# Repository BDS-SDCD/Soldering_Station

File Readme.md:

# MAIN

 This soldering station developed for the handle of the Hakko T12 soldering iron (needs to be modified according to the given scheme) Heat gun with the 8858 substation (~220 spiral 12V fan). Anything that can heat up from ~220 and has a thermocouple will do as a soldering separator. In my case, it is literally an iron. This project was developed for home made one layer PCB based on photoresist technology and using the element base that is already available.<br/>

[Schematic](https://github.com/BDS-SDCD/Soldering_Station/tree/main/Station%20Schematic/Chematic%20PDF)<br/>
[Code](https://github.com/BDS-SDCD/Soldering_Station/tree/main/Station%20Code/Core)<br/>

### Features

 Each of the devices has a set of settings. As a rule, when I’m working with a soldering station, I use only a few temperature settings, which are implemented here in adjustable temperature presets. Each of the presets has its own temperature correction value, which allows you to accurately adjust the temperature of each preset. Also, the manual control mode has a separate temperature correction value.

In this project I did not provide the ability to configure important parameters such as the PID controller coefficient and the temperature conversion coefficient in the user interface. All this can be configured in the [Soldering_Station.h](https://github.com/BDS-SDCD/Soldering_Station/blob/main/Station%20Code/Core/Inc/Soldering_Station.h) file by changing the Define value. Also you can change Button mapping of presets in this file. Everything else is configured inside the user interface.

All interfaces are symbolic.

 Switching on/off any soldering device can be done either by additional methods or by short pressing the encoder. Switching control between the heat gun and the soldering separator can be done by holding the encoder SW1. Switching temperature settings as well as setting the temperature of the manual mode is done only when the soldering device is turned on.

 Holding the SW4 encoder will lead to the transition to the menu with devices and their parameters. The transition from the menu to the previous menu is carried out by holding the SW4 encoder. When setting the value, several step modifiers are available by pressing buttons SW8 and SW2. The standard value is x1. When pressing button SW8, the modifier changes to x2. When you press SW8 button again, the modifier will return. SW8 button with the x5 modifier works the same way. If you turn on 2 modifiers in a free order, you will get a x10 modifier.

### Soldering iron

 The advantages include the fact that, unlike the original Chinese Hakko T12 controller, you will no longer be able to hear annoying clicks during heating, since here PWM is used to control the soldering iron. The PWM frequency is 24 kHz. Unlike the basic version of the soldering iron controller, it has the ability to press a button on the soldering iron to set the maximum temperature for heating massive soldering pads. The implementation of the button is the setting of the maximum temperature that the ADC can process. When implementing the supply of full power without regulation, it led me to several broken soldering tips.

### Soldering Heat Gun

 As a control system for heating the heat gun, as well as the soldering separator, the Phase Angle Control(PAC) system is used. The control module for the air flow rate of the heat gun is completely linear and analog, which leads to the need to install a radiator on the MOSFET. Setting the minimum flow rate(RV6), as well as the maximum flow rate(RV4), is adjusted by variable resistors. A separate variable resistor is used to control the manual flow rate(RV3). The system automatically sets the maximum air flow rate during the cooling of the heat gun after switching off. Switching on/off can be done either from the control panel or by uninstalling/installing the heat gun on the stand. Ideally, the power part of the heat gun control should be connected so that the phase is broken, which in this case will ensure safe contact with the socket with the soldering station connected to the power.

### Soldering separator.

 An old iron is used as a soldering separator in this project. This is the only test subject that survived many heating and cooling cycles, since the melting temperature of the soldering mouth is 187 degrees, and when soldering BGA chips, 270. Like the heat gun, the control system based on PAC. Switching on/off can be done either from the control panel.

### Update<br/>

The PAC implementation has been changed from software to hardware. The input capture and PAC system is implemented based on the signal capture and PWM modes. 

### Further development.

 The schematic provides for a ventilation control system. Since the Hakko T12 soldering iron can be modified similarly to the 908b Soldering iron smoke absorber. Since the project is being done primarily for myself, I have not yet decided which type of ventilation will be more convenient for me.

 In the future, schematic of this module will be changed depending on my experience of use. At those moment, there is no software implementation of this unit.
In case of inconvenience during regular work, modification or replacement of the symbolic interface with a graphical one.
Also, if necessary, other functionality will be added.

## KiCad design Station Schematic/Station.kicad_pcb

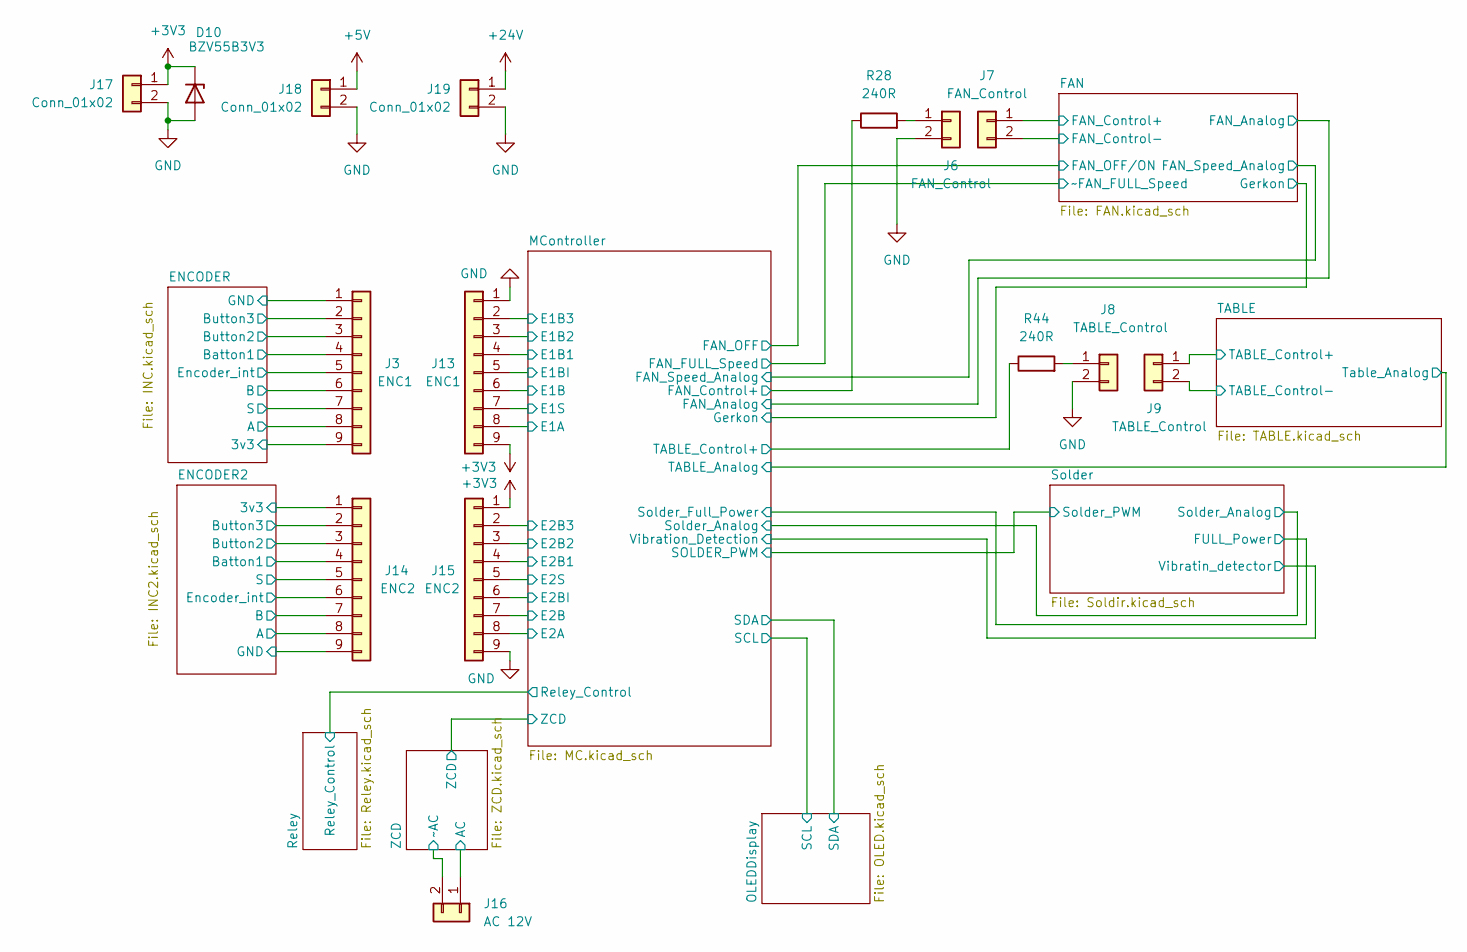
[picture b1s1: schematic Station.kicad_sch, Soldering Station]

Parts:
D10: BZV55B3V3; D_MiniMELF
J3: ENC1; PinSocket_1x09_P2.54mm_Vertical
J6: FAN_Control; PinHeader_1x02_P2.54mm_Vertical
J7: FAN_Control; PinSocket_1x02_P2.54mm_Vertical
J8: TABLE_Control; PinHeader_1x02_P2.54mm_Vertical
J9: TABLE_Control; PinSocket_1x02_P2.54mm_Vertical
J13: ENC1; PinHeader_1x09_P2.54mm_Vertical
J14: ENC2; PinSocket_1x09_P2.54mm_Vertical
J15: ENC2; PinHeader_1x09_P2.54mm_Vertical
J16: AC 12V; TerminalBlock_4Ucon_1x02_P3.50mm_Horizontal
J17, J18, J19: Conn_01x02; PhoenixContact_GMSTBVA_2,5_2-G_1x02_P7.50mm_Vertical
R28, R44: 240R; R_1206_3216Metric_Pad1.30x1.75mm_HandSolder

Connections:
+3V3: D10.1 (K), J13.9, J15.1, J17.1; also elsewhere on the board
+5V: J18.1; also elsewhere on the board
+24V: J19.1; also elsewhere on the board
/ENCODER2/3v3: J14.1; also elsewhere on the board
/ENCODER2/A: J14.8; also elsewhere on the board
/ENCODER2/B: J14.7; also elsewhere on the board
/ENCODER2/Batton1: J14.4; also elsewhere on the board
/ENCODER2/Button2: J14.3; also elsewhere on the board
/ENCODER2/Button3: J14.2; also elsewhere on the board
/ENCODER2/Encoder_int: J14.6; also elsewhere on the board
/ENCODER2/GND: J14.9; also elsewhere on the board
/ENCODER2/S: J14.5; also elsewhere on the board
/ENCODER/3v3: J3.9; also elsewhere on the board
/ENCODER/A: J3.8; also elsewhere on the board
/ENCODER/B: J3.6; also elsewhere on the board
/ENCODER/Batton1: J3.4; also elsewhere on the board
/ENCODER/Button2: J3.3; also elsewhere on the board
/ENCODER/Button3: J3.2; also elsewhere on the board
/ENCODER/Encoder_int: J3.5; also elsewhere on the board
/ENCODER/GND: J3.1; also elsewhere on the board
/ENCODER/S: J3.7; also elsewhere on the board
/FAN/FAN_Control+: J7.1; also elsewhere on the board
/FAN/FAN_Control-: J7.2; also elsewhere on the board
/MController/E1A: J13.8; also elsewhere on the board
/MController/E1B: J13.6; also elsewhere on the board
/MController/E1B1: J13.4; also elsewhere on the board
/MController/E1B2: J13.3; also elsewhere on the board
/MController/E1B3: J13.2; also elsewhere on the board
/MController/E1BI: J13.5; also elsewhere on the board
/MController/E1S: J13.7; also elsewhere on the board
/MController/E2A: J15.8; also elsewhere on the board
/MController/E2B: J15.7; also elsewhere on the board
/MController/E2B1: J15.4; also elsewhere on the board
/MController/E2B2: J15.3; also elsewhere on the board
/MController/E2B3: J15.2; also elsewhere on the board
/MController/E2BI: J15.6; also elsewhere on the board
/MController/E2S: J15.5; also elsewhere on the board
/MController/FAN_Control+: R28.1; also elsewhere on the board
/MController/TABLE_Control+: R44.1; also elsewhere on the board
/TABLE/TABLE_Control+: J9.1; also elsewhere on the board
/TABLE/TABLE_Control-: J9.2; also elsewhere on the board
/ZCD/AC: J16.1; also elsewhere on the board
/ZCD/~AC: J16.2; also elsewhere on the board
GND: D10.2 (A), J6.2, J8.2, J13.1, J15.9, J17.2, J18.2, J19.2; also elsewhere on the board
unnamed: J6.1, R28.2
unnamed: J8.1, R44.2

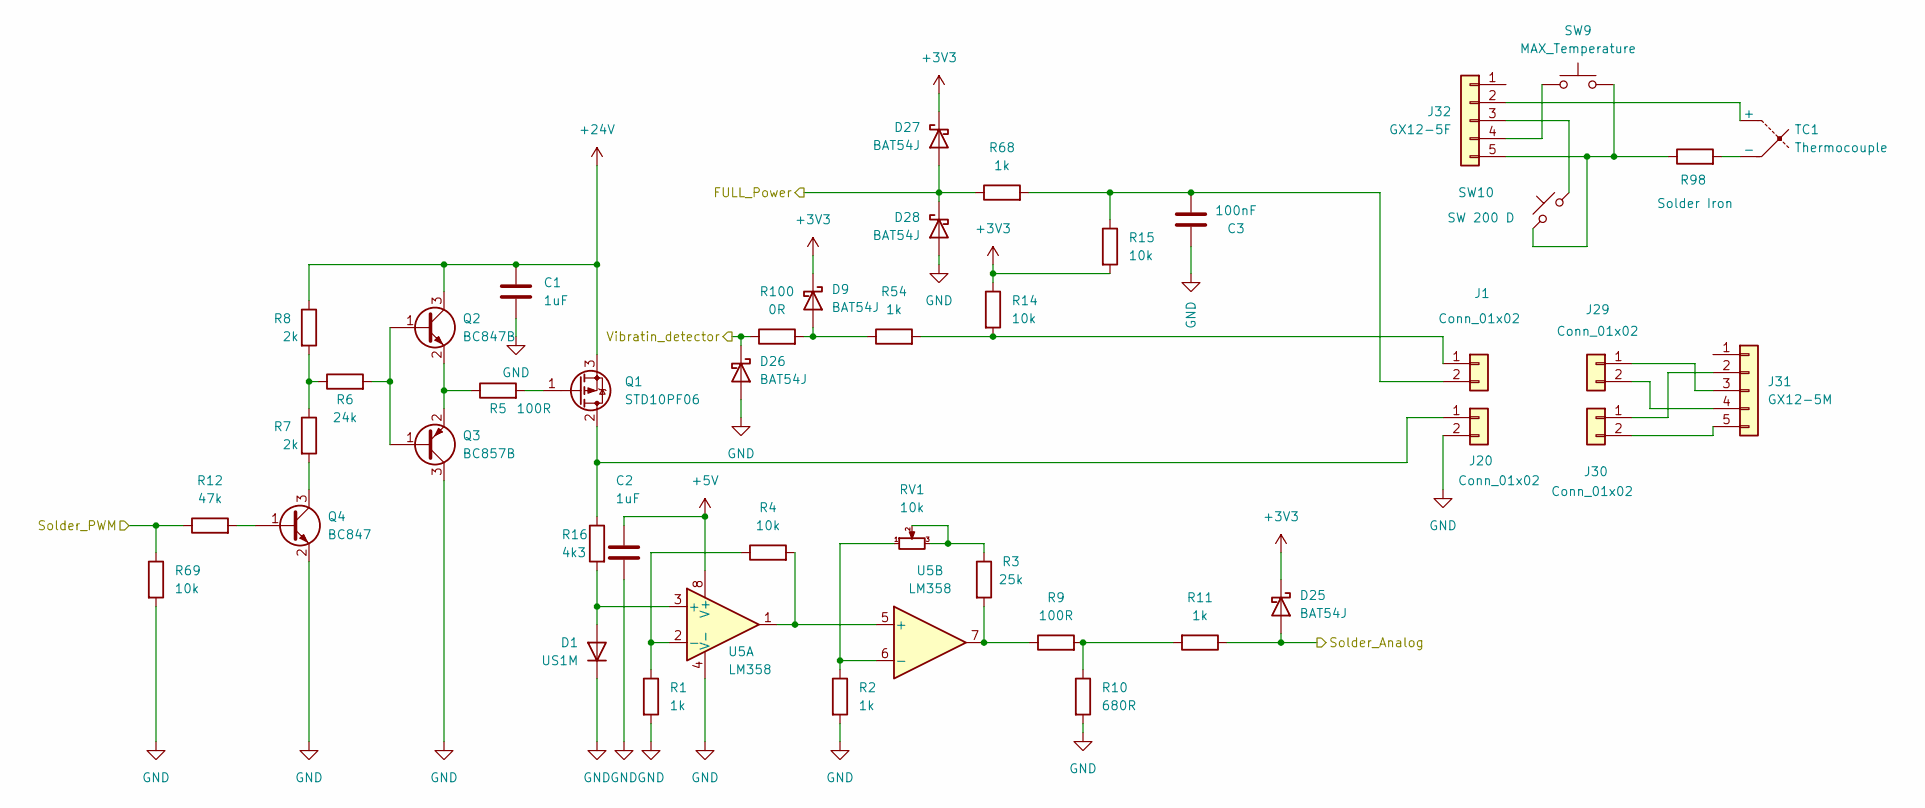
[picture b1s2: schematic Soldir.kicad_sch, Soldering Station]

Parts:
C1, C2: 1uF; C_1206_3216Metric
C3: 100nF; C_1206_3216Metric
D1: US1M; D_SMA
D9, D25, D26, D27, D28: BAT54J; D_SOD-323F
J1, J29: Conn_01x02; PinHeader_1x02_P2.54mm_Vertical
J20, J30: Conn_01x02; PhoenixContact_GMSTBVA_2,5_2-G_1x02_P7.50mm_Vertical
J31: GX12-5M
J32: GX12-5F
Q1: STD10PF06; TO-252-2
Q2: BC847B; TSOT-23
Q3: BC857B; TSOT-23
Q4: BC847; TSOT-23
R1, R2, R11, R54, R68: 1k; R_1206_3216Metric_Pad1.30x1.75mm_HandSolder
R3: 25k; R_1206_3216Metric_Pad1.30x1.75mm_HandSolder
R4, R14, R15, R69: 10k; R_1206_3216Metric_Pad1.30x1.75mm_HandSolder
R5, R9: 100R; R_1206_3216Metric_Pad1.30x1.75mm_HandSolder
R6: 24k; R_1206_3216Metric_Pad1.30x1.75mm_HandSolder
R7, R8: 2k; R_1206_3216Metric_Pad1.30x1.75mm_HandSolder
R10: 680R; R_1206_3216Metric_Pad1.30x1.75mm_HandSolder
R12: 47k; R_1206_3216Metric_Pad1.30x1.75mm_HandSolder
R16: 4k3; R_1206_3216Metric_Pad1.30x1.75mm_HandSolder
R98: Solder Iron
R100: 0R; R0 16.128
RV1: 10k; Potentiometer_Bourns_3266Y_Vertical
SW9: MAX_Temperature
SW10: SW 200 D
TC1: Thermocouple
U5: LM358; SOIC-8_3.9x4.9mm_P1.27mm

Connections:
+3V3: D9.1 (K), D25.1 (K), D27.1 (K), R14.1, R15.2; also elsewhere on the board
+5V: C2.1, U5.8 (V+); also elsewhere on the board
+24V: C1.1, Q1.3 (S1), Q2.3 (C), R8.1; also elsewhere on the board
/MController/SOLDER_PWM: R12.1, R69.1; also elsewhere on the board
/MController/Solder_Analog: D25.2 (A), R11.1; also elsewhere on the board
/MController/Solder_Full_Power: D27.2 (A), D28.1 (K), R68.1; also elsewhere on the board
/MController/Vibration_Detection: D26.1 (K), R100.1; also elsewhere on the board
GND: C1.2, C2.2, C3.2, D1.1 (K), D26.2 (A), D28.2 (A), J20.2, Q3.3 (C), Q4.2 (E), R1.2, R2.2, R10.2, R69.2, U5.4 (V-); also elsewhere on the board
unnamed: D1.2 (A), R16.2, U5.3 (+)
unnamed: D9.2 (A), R54.1, R100.2
unnamed: J1.1, R14.2, R54.2
unnamed: C3.1, J1.2, R15.1, R68.2
unnamed: J20.1, Q1.2 (D1), R16.1
unnamed: J29.1, J31.3
unnamed: J29.2, J31.4
unnamed: J30.1, J31.2
unnamed: J30.2, J31.5
unnamed: J32.2, TC1.1 (+)
unnamed: J32.3, SW10.2
unnamed: J32.4, SW9.1
unnamed: J32.5, R98.1, SW9.2, SW10.1
unnamed: Q1.1 (G2), R5.2
unnamed: Q2.1 (B), Q3.1 (B), R6.2
unnamed: Q2.2 (E), Q3.2 (E), R5.1
unnamed: Q4.1 (B), R12.2
unnamed: Q4.3 (C), R7.2
unnamed: R3.1, RV1.2, RV1.3
unnamed: R3.2, R9.1, U5.7
unnamed: R6.1, R7.1, R8.2
unnamed: R9.2, R10.1, R11.2
unnamed: R98.2, TC1.2 (-)
unnamed: R1.1, R4.1, U5.2 (-)
unnamed: R4.2, U5.1, U5.5 (+)
unnamed: R2.1, RV1.1, U5.6 (-)

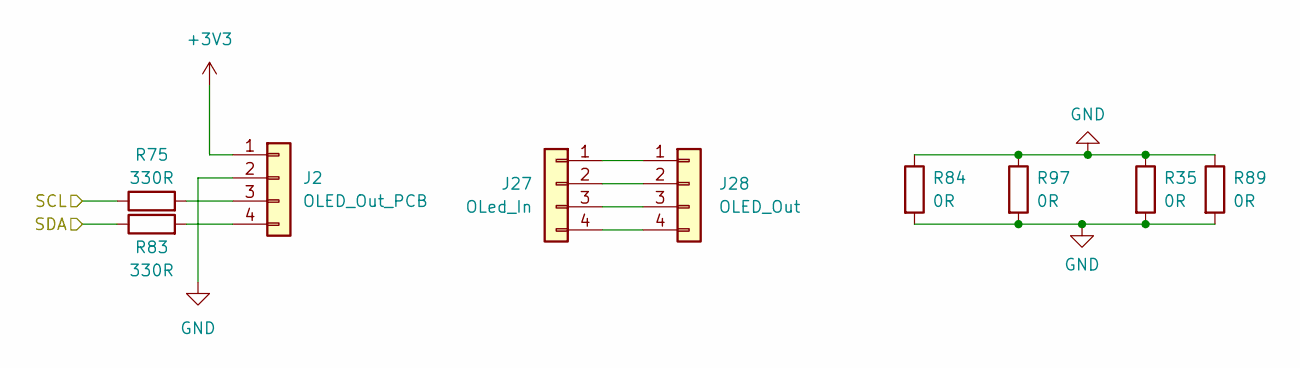
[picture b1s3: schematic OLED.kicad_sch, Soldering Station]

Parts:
J2: OLED_Out_PCB; PinHeader_1x04_P2.54mm_Vertical
J27: OLed_In; PinHeader_1x04_P2.54mm_Vertical
J28: OLED_Out; PinSocket_1x04_P2.54mm_Vertical
R35, R84, R89, R97: 0R; R_1206_3216Metric_Pad1.30x1.75mm_HandSolder
R75, R83: 330R; R_1206_3216Metric_Pad1.30x1.75mm_HandSolder

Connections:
+3V3: J2.1; also elsewhere on the board
/MController/SCL: R75.1; also elsewhere on the board
/MController/SDA: R83.1; also elsewhere on the board
GND: J2.2, R35.1, R35.2, R84.1, R84.2, R89.1, R89.2, R97.1, R97.2; also elsewhere on the board
unnamed: J2.3, R75.2
unnamed: J2.4, R83.2
unnamed: J27.1, J28.1
unnamed: J27.2, J28.2
unnamed: J27.3, J28.3
unnamed: J27.4, J28.4

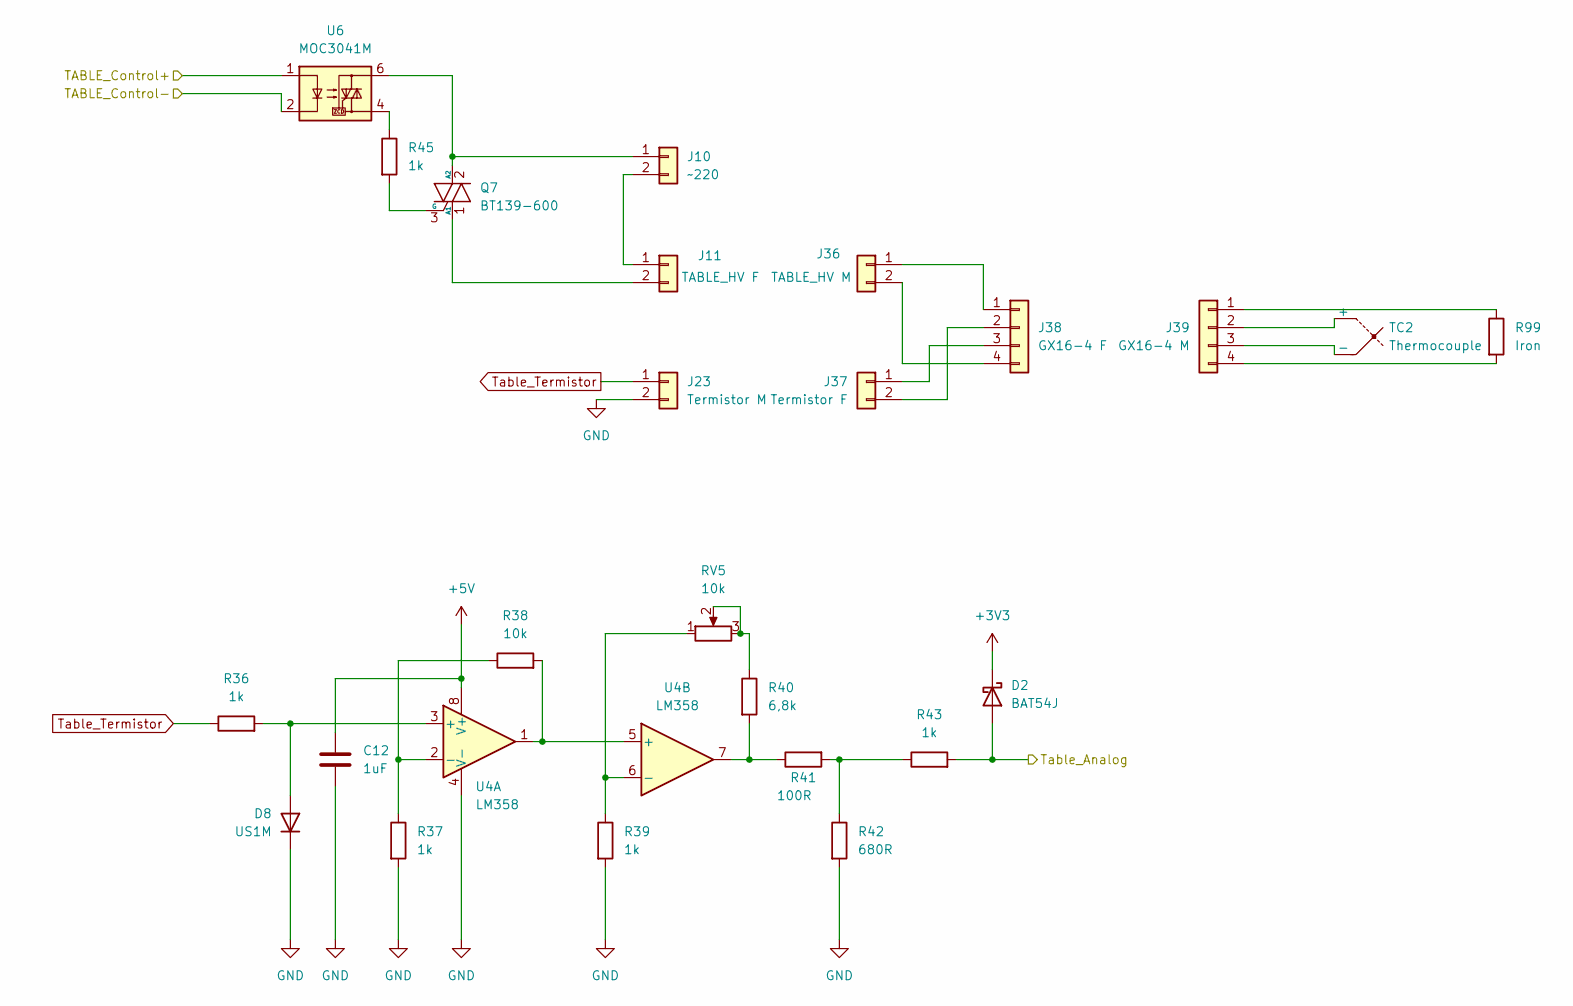
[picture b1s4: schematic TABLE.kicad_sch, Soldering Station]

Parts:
C12: 1uF; C_1206_3216Metric
D2: BAT54J; D_SOD-323F
D8: US1M; D_SMA
J10: ~220; PhoenixContact_GMSTBVA_2,5_2-G_1x02_P7.50mm_Vertical
J11: TABLE_HV F; PhoenixContact_GMSTBVA_2,5_2-G_1x02_P7.50mm_Vertical
J23: Termistor M; PinHeader_1x02_P2.54mm_Vertical
J36: TABLE_HV M; PhoenixContact_GMSTBVA_2,5_2-G_1x02_P7.50mm_Vertical
J37: Termistor F; PinHeader_1x02_P2.54mm_Vertical
J38: GX16-4 F
J39: GX16-4 M
Q7: BT139-600; TO-220-3_Vertical
R36, R37, R39, R43: 1k; R_1206_3216Metric_Pad1.30x1.75mm_HandSolder
R38: 10k; R_1206_3216Metric_Pad1.30x1.75mm_HandSolder
R40: 6,8k; R_1206_3216Metric_Pad1.30x1.75mm_HandSolder
R41: 100R; R_1206_3216Metric_Pad1.30x1.75mm_HandSolder
R42: 680R; R_1206_3216Metric_Pad1.30x1.75mm_HandSolder
R45: 1k; R_Axial_Power_L25.0mm_W9.0mm_P30.48mm
R99: Iron
RV5: 10k; Potentiometer_Bourns_3266Y_Vertical
TC2: Thermocouple
U4: LM358; SOIC-8_3.9x4.9mm_P1.27mm
U6: MOC3041M; DIP-6_W7.62mm_LongPads

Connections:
+3V3: D2.1 (K); also elsewhere on the board
+5V: C12.1, U4.8 (V+); also elsewhere on the board
/MController/TABLE_Analog: D2.2 (A), R43.2; also elsewhere on the board
/TABLE/TABLE_Control+: U6.1; also elsewhere on the board
/TABLE/TABLE_Control-: U6.2; also elsewhere on the board
GND: C12.2, D8.1 (K), J23.2, R37.2, R39.2, R42.2, U4.4 (V-); also elsewhere on the board
unnamed: D8.2 (A), R36.2, U4.3 (+)
unnamed: J10.1, Q7.2 (A2), U6.6
unnamed: J10.2, J11.1
unnamed: J11.2, Q7.1 (A1)
unnamed: J36.1, J38.1
unnamed: J36.2, J38.4
unnamed: J37.1, J38.3
unnamed: J37.2, J38.2
unnamed: J39.1, R99.1
unnamed: J39.2, TC2.1 (+)
unnamed: J39.3, TC2.2 (-)
unnamed: J39.4, R99.2
unnamed: Q7.3 (G), R45.2
unnamed: R40.1, RV5.2, RV5.3
unnamed: R40.2, R41.1, U4.7
unnamed: R41.2, R42.1, R43.1
unnamed: R45.1, U6.4
unnamed: R37.1, R38.1, U4.2 (-)
unnamed: R38.2, U4.1, U4.5 (+)
unnamed: R39.1, RV5.1, U4.6 (-)
Table_Termistor: J23.1, R36.1

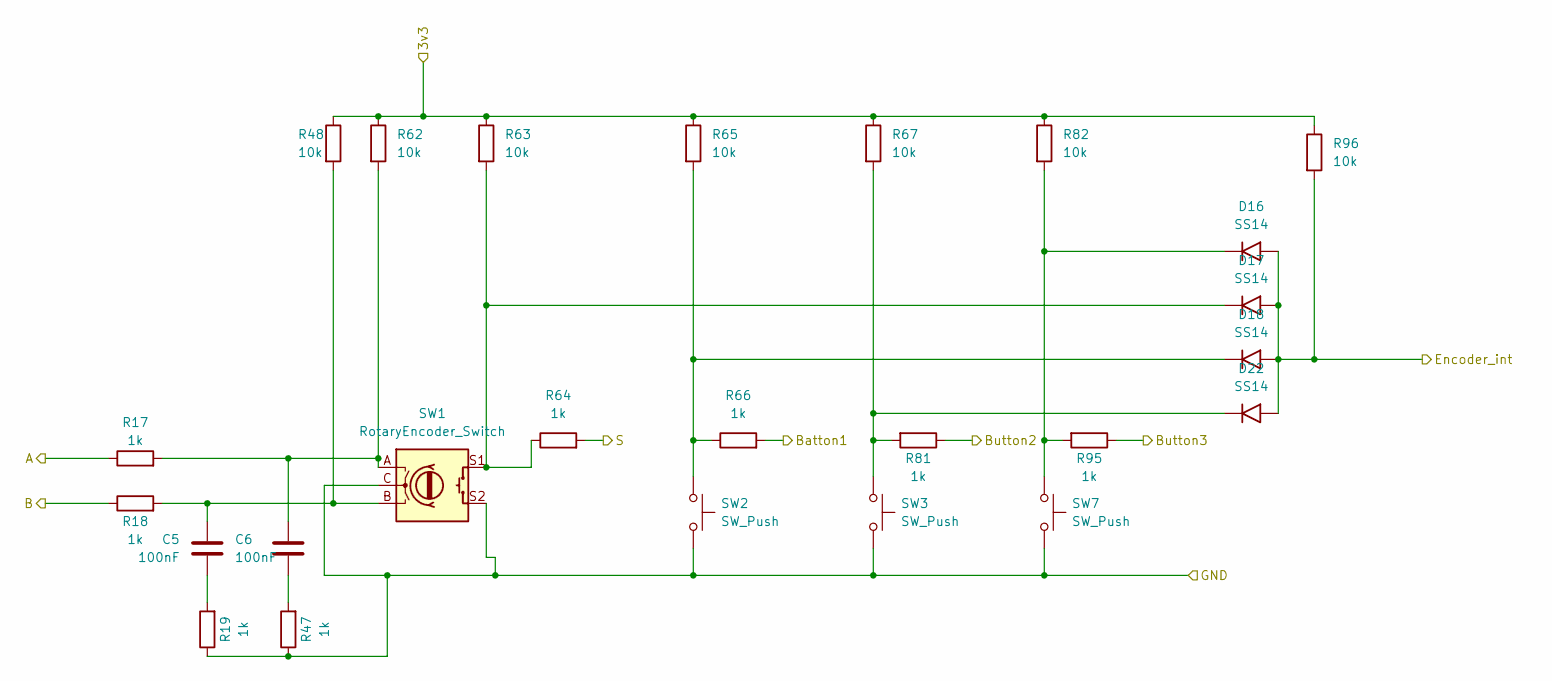
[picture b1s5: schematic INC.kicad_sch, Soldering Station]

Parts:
C5, C6: 100nF; C_1206_3216Metric
D16, D17, D18, D22: SS14; D_SMA
R17, R18, R19, R47, R64, R66, R81, R95: 1k; R_1206_3216Metric_Pad1.30x1.75mm_HandSolder
R48, R62, R63, R65, R67, R82, R96: 10k; R_1206_3216Metric_Pad1.30x1.75mm_HandSolder
SW1: RotaryEncoder_Switch; RotaryEncoder_Bourns_Vertical_PEC12R-3x17F-Sxxxx
SW2, SW3, SW7: SW_Push; SW_PUSH_6mm

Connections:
/ENCODER/3v3: R48.1, R62.1, R63.1, R65.1, R67.1, R82.1, R96.1; also elsewhere on the board
/ENCODER/A: R17.1; also elsewhere on the board
/ENCODER/B: R18.1; also elsewhere on the board
/ENCODER/Batton1: R66.2; also elsewhere on the board
/ENCODER/Button2: R81.1; also elsewhere on the board
/ENCODER/Button3: R95.1; also elsewhere on the board
/ENCODER/Encoder_int: D16.2 (A), D17.2 (A), D18.2 (A), D22.2 (A), R96.2; also elsewhere on the board
/ENCODER/GND: R19.1, R47.1, SW1.C, SW1.S2, SW2.2, SW3.2, SW7.2; also elsewhere on the board
/ENCODER/S: R64.2; also elsewhere on the board
unnamed: C5.1, R18.2, R48.2, SW1.B
unnamed: C5.2, R19.2
unnamed: C6.1, R17.2, R62.2, SW1.A
unnamed: C6.2, R47.2
unnamed: D16.1 (K), R82.2, R95.2, SW7.1
unnamed: D17.1 (K), R63.2, R64.1, SW1.S1
unnamed: D18.1 (K), R65.2, R66.1, SW2.1
unnamed: D22.1 (K), R67.2, R81.2, SW3.1

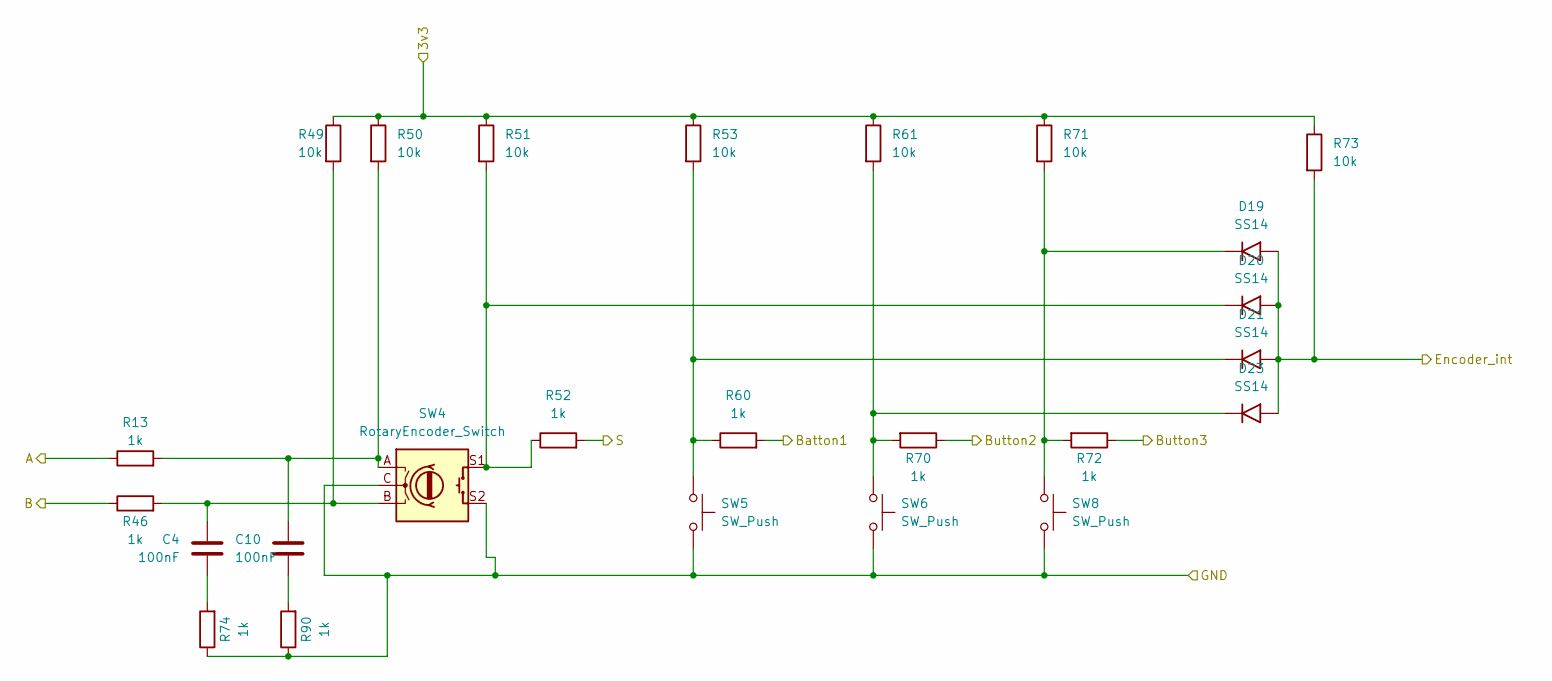
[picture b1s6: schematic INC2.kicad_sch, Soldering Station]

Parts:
C4, C10: 100nF; C_1206_3216Metric
D19, D20, D21, D23: SS14; D_SMA
R13, R46, R52, R60, R70, R72, R74, R90: 1k; R_1206_3216Metric_Pad1.30x1.75mm_HandSolder
R49, R50, R51, R53, R61, R71, R73: 10k; R_1206_3216Metric_Pad1.30x1.75mm_HandSolder
SW4: RotaryEncoder_Switch; RotaryEncoder_Bourns_Vertical_PEC12R-3x17F-Sxxxx
SW5, SW6, SW8: SW_Push; SW_PUSH_6mm

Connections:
/ENCODER2/3v3: R49.1, R50.1, R51.1, R53.1, R61.1, R71.1, R73.1; also elsewhere on the board
/ENCODER2/A: R13.1; also elsewhere on the board
/ENCODER2/B: R46.1; also elsewhere on the board
/ENCODER2/Batton1: R60.2; also elsewhere on the board
/ENCODER2/Button2: R70.1; also elsewhere on the board
/ENCODER2/Button3: R72.1; also elsewhere on the board
/ENCODER2/Encoder_int: D19.2 (A), D20.2 (A), D21.2 (A), D23.2 (A), R73.2; also elsewhere on the board
/ENCODER2/GND: R74.1, R90.1, SW4.C, SW4.S2, SW5.2, SW6.2, SW8.2; also elsewhere on the board
/ENCODER2/S: R52.2; also elsewhere on the board
unnamed: C4.1, R46.2, R49.2, SW4.B
unnamed: C4.2, R74.2
unnamed: C10.1, R13.2, R50.2, SW4.A
unnamed: C10.2, R90.2
unnamed: D19.1 (K), R71.2, R72.2, SW8.1
unnamed: D20.1 (K), R51.2, R52.1, SW4.S1
unnamed: D21.1 (K), R53.2, R60.1, SW5.1
unnamed: D23.1 (K), R61.2, R70.2, SW6.1

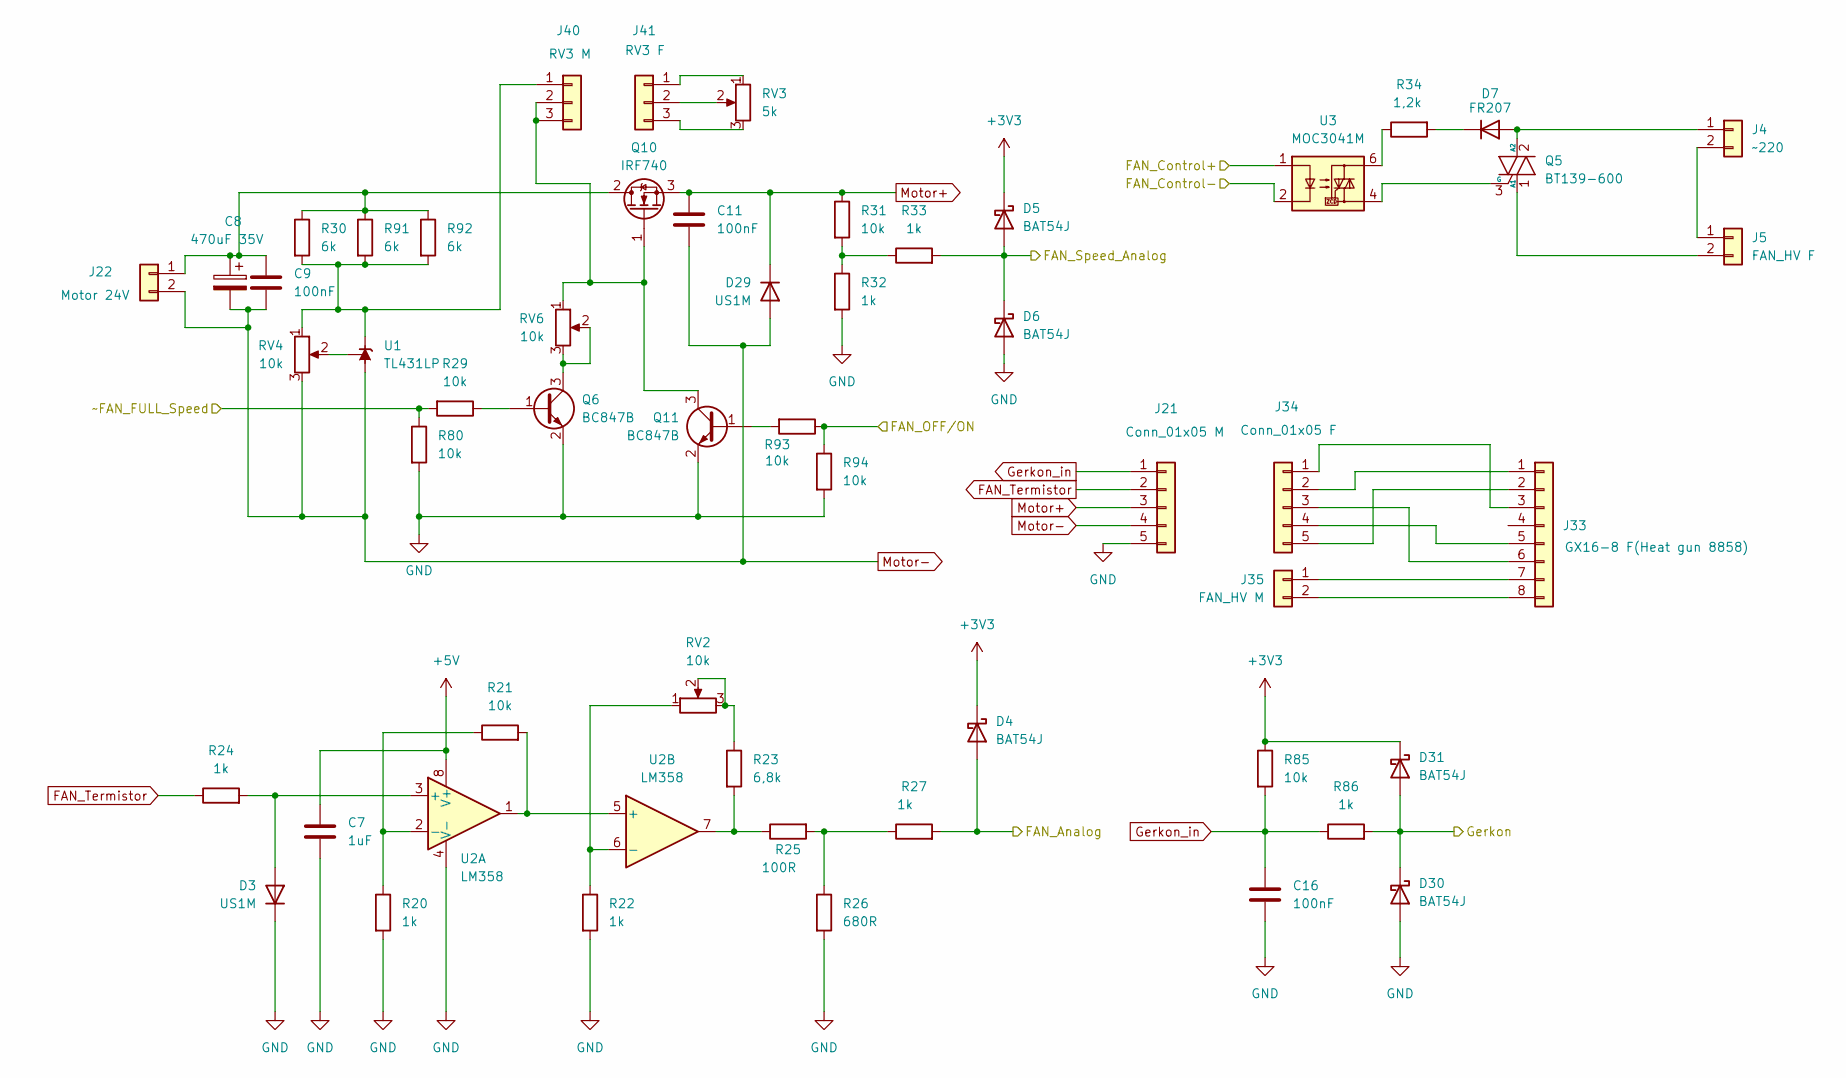
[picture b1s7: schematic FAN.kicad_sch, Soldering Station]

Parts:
C7: 1uF; C_1206_3216Metric
C8: 470uF 35V; CP_Radial_Tantal_D10.5mm_P5.00mm
C9, C11, C16: 100nF; C_1206_3216Metric
D3, D29: US1M; D_SMA
D4, D5, D6, D30, D31: BAT54J; D_SOD-323F
D7: FR207; D_DO-15_P10.16mm_Horizontal
J4: ~220; PhoenixContact_GMSTBVA_2,5_2-G_1x02_P7.50mm_Vertical
J5: FAN_HV F; PhoenixContact_GMSTBVA_2,5_2-G_1x02_P7.50mm_Vertical
J21: Conn_01x05 M; PinHeader_1x05_P2.54mm_Vertical
J22: Motor 24V; PhoenixContact_GMSTBVA_2,5_2-G_1x02_P7.50mm_Vertical
J33: GX16-8 F(Heat gun 8858)
J34: Conn_01x05 F
J35: FAN_HV M; PhoenixContact_GMSTBVA_2,5_2-G_1x02_P7.50mm_Vertical
J40: RV3 M; PinHeader_1x03_P2.54mm_Vertical
J41: RV3 F; PinSocket_1x03_P2.54mm_Vertical
Q5: BT139-600; TO-220-3_Vertical
Q6, Q11: BC847B; SOT-23
Q10: IRF740; TO-220-3_Vertical
R20, R22, R24, R27, R32, R33, R86: 1k; R_1206_3216Metric_Pad1.30x1.75mm_HandSolder
R21, R29, R31, R80, R85, R93, R94: 10k; R_1206_3216Metric_Pad1.30x1.75mm_HandSolder
R23: 6,8k; R_1206_3216Metric_Pad1.30x1.75mm_HandSolder
R25: 100R; R_1206_3216Metric_Pad1.30x1.75mm_HandSolder
R26: 680R; R_1206_3216Metric_Pad1.30x1.75mm_HandSolder
R30, R91, R92: 6k; R_1206_3216Metric_Pad1.30x1.75mm_HandSolder
R34: 1,2k; R_Axial_Power_L25.0mm_W9.0mm_P30.48mm
RV2, RV4, RV6: 10k; Potentiometer_Bourns_3266Y_Vertical
RV3: 5k; Potentiometer_Bourns_3266Y_Vertical
U1: TL431LP; TO-92_Inline
U2: LM358; SOIC-8_3.9x4.9mm_P1.27mm
U3: MOC3041M; DIP-6_W7.62mm_LongPads

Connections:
+3V3: D4.1 (K), D5.1 (K), D31.1 (K), R85.1; also elsewhere on the board
+5V: C7.1, U2.8 (V+); also elsewhere on the board
/FAN/FAN_Analog: D4.2 (A), R27.2; also elsewhere on the board
/FAN/FAN_Control+: U3.1; also elsewhere on the board
/FAN/FAN_Control-: U3.2; also elsewhere on the board
/FAN/FAN_OFF/ON: R93.1, R94.1; also elsewhere on the board
/FAN/FAN_Speed_Analog: D5.2 (A), D6.1 (K), R33.2; also elsewhere on the board
/FAN/Gerkon: D30.1 (K), D31.2 (A), R86.2; also elsewhere on the board
/FAN/~FAN_FULL_Speed: R29.2, R80.1; also elsewhere on the board
FAN_Termistor: J21.2, R24.1
GND: C7.2, C16.2, D3.1 (K), D6.2 (A), D30.2 (A), J21.5, Q6.2 (E), Q11.2 (E), R20.2, R22.2, R26.2, R32.2, R80.2, R94.2, U2.4 (V-); also elsewhere on the board
Gerkon_in: C16.1, J21.1, R85.2, R86.1
Motor+: C11.1, D29.1 (K), J21.3, Q10.3 (S), R31.1
Motor-: C8.2, C9.2, C11.2, D29.2 (A), J21.4, J22.2, RV4.3, U1.2 (A)
unnamed: D3.2 (A), R24.2, U2.3 (+)
unnamed: D7.2 (A), J4.1, Q5.2 (A2)
unnamed: D7.1 (K), R34.2
unnamed: J4.2, J5.1
unnamed: J5.2, Q5.1 (A1)
unnamed: C8.1, C9.1, J22.1, Q10.2 (D), R30.1, R91.1, R92.1
unnamed: J33.1, J34.2
unnamed: J33.2, J34.5
unnamed: J33.3, J34.1
unnamed: J33.5, J34.4
unnamed: J33.6, J34.3
unnamed: J33.7, J35.1
unnamed: J33.8, J35.2
unnamed: J40.1, R30.2, R91.2, R92.2, RV4.1, U1.3 (K)
unnamed: J40.2, J40.3, Q10.1 (G), Q11.3 (C), RV6.1
unnamed: J41.1, RV3.1
unnamed: J41.2, RV3.2
unnamed: J41.3, RV3.3
unnamed: Q5.3 (G), U3.4
unnamed: Q6.1 (B), R29.1
unnamed: Q6.3 (C), RV6.2, RV6.3
unnamed: Q11.1 (B), R93.2
unnamed: R23.1, RV2.2, RV2.3
unnamed: R23.2, R25.1, U2.7
unnamed: R25.2, R26.1, R27.1
unnamed: R31.2, R32.1, R33.1
unnamed: R34.1, U3.6
unnamed: RV4.2, U1.1 (REF)
unnamed: R20.1, R21.1, U2.2 (-)
unnamed: R21.2, U2.1, U2.5 (+)
unnamed: R22.1, RV2.1, U2.6 (-)

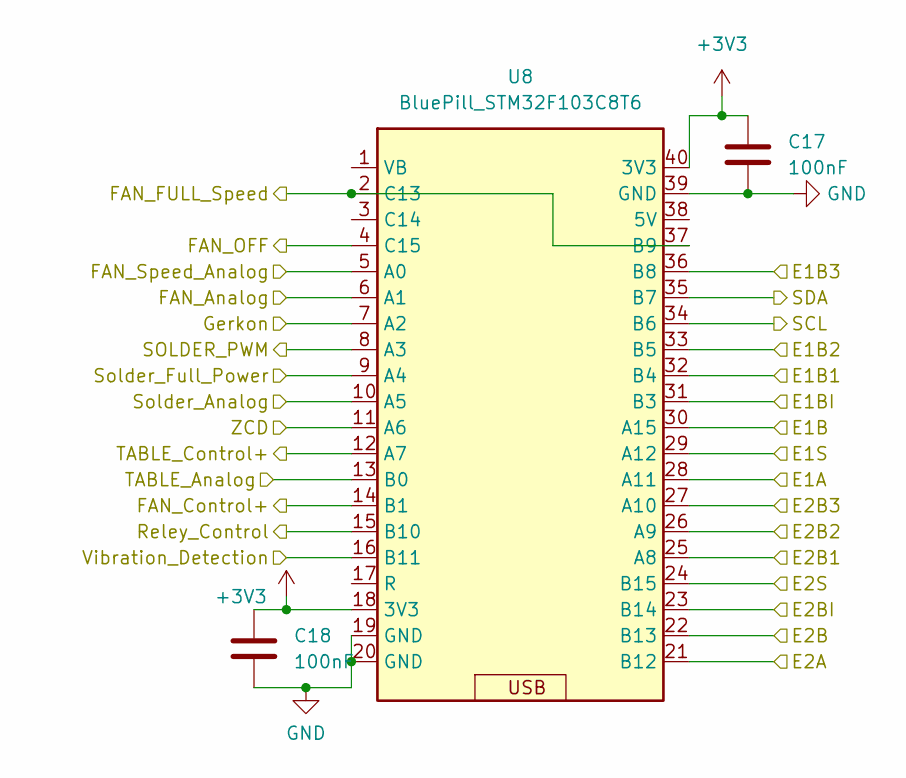
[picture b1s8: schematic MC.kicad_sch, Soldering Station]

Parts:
C17, C18: 100nF; C_1206_3216Metric
U8: BluePill_STM32F103C8T6; BLUEPILL_STM32

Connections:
+3V3: C17.1, C18.1, U8.18 (3V3), U8.40 (3V3); also elsewhere on the board
/FAN/FAN_Analog: U8.6 (A1); also elsewhere on the board
/FAN/FAN_OFF/ON: U8.4 (C15); also elsewhere on the board
/FAN/FAN_Speed_Analog: U8.5 (A0); also elsewhere on the board
/FAN/Gerkon: U8.7 (A2); also elsewhere on the board
/FAN/~FAN_FULL_Speed: U8.2 (C13), U8.37 (B9); also elsewhere on the board
/MController/E1A: U8.28 (A11); also elsewhere on the board
/MController/E1B: U8.30 (A15); also elsewhere on the board
/MController/E1B1: U8.32 (B4); also elsewhere on the board
/MController/E1B2: U8.33 (B5); also elsewhere on the board
/MController/E1B3: U8.36 (B8); also elsewhere on the board
/MController/E1BI: U8.31 (B3); also elsewhere on the board
/MController/E1S: U8.29 (A12); also elsewhere on the board
/MController/E2A: U8.21 (B12); also elsewhere on the board
/MController/E2B: U8.22 (B13); also elsewhere on the board
/MController/E2B1: U8.25 (A8); also elsewhere on the board
/MController/E2B2: U8.26 (A9); also elsewhere on the board
/MController/E2B3: U8.27 (A10); also elsewhere on the board
/MController/E2BI: U8.23 (B14); also elsewhere on the board
/MController/E2S: U8.24 (B15); also elsewhere on the board
/MController/FAN_Control+: U8.14 (B1); also elsewhere on the board
/MController/Reley_Control: U8.15 (B10); also elsewhere on the board
/MController/SCL: U8.34 (B6); also elsewhere on the board
/MController/SDA: U8.35 (B7); also elsewhere on the board
/MController/SOLDER_PWM: U8.8 (A3); also elsewhere on the board
/MController/Solder_Analog: U8.10 (A5); also elsewhere on the board
/MController/Solder_Full_Power: U8.9 (A4); also elsewhere on the board
/MController/TABLE_Analog: U8.13 (B0); also elsewhere on the board
/MController/TABLE_Control+: U8.12 (A7); also elsewhere on the board
/MController/Vibration_Detection: U8.16 (B11); also elsewhere on the board
/MController/ZCD: U8.11 (A6); also elsewhere on the board
GND: C17.2, C18.2, U8.19 (GND), U8.20 (GND), U8.39 (GND); also elsewhere on the board

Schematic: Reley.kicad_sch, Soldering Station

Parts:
J12: Conn_01x02; PhoenixContact_GMSTBVA_2,5_2-G_1x02_P7.50mm_Vertical
J24, J25: Reley_Control; PinHeader_1x02_P2.54mm_Vertical
J26: Reley24V; PhoenixContact_GMSTBVA_2,5_2-G_1x02_P7.50mm_Vertical
K1: Relay_SPDT; Relay_SPDT_Finder_36.11
Q8: NPN; TSOT-23
Q9: NoName; TO-252-2
R76: 51k; R_1206_3216Metric_Pad1.30x1.75mm_HandSolder
R77: 10k; R_1206_3216Metric_Pad1.30x1.75mm_HandSolder
R78, R79: 4.7k; R_1206_3216Metric_Pad1.30x1.75mm_HandSolder

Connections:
/MController/Reley_Control: R76.1, R77.1; also elsewhere on the board
GND: J24.2, R77.2; also elsewhere on the board
unnamed: J12.1, K1.14
unnamed: J12.2, K1.11
unnamed: J24.1, R76.2
unnamed: J25.1, Q8.2 (B)
unnamed: J25.2, J26.2, K1.A2, Q8.3 (E)
unnamed: J26.1, Q9.3 (S1), R79.1
unnamed: Q8.1 (C), R78.2
unnamed: K1.A1, Q9.2 (D1)
unnamed: Q9.1 (G2), R78.1, R79.2

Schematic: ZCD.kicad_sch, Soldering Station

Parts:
C23: 100nF; C_1206_3216Metric
D11, D12, D13, D14, D15: SS14; D_SMA
D24: BZV55B3V3; D_MiniMELF
R55: 10k; R_1206_3216Metric_Pad1.30x1.75mm_HandSolder
R56: 100R; R_1206_3216Metric_Pad1.30x1.75mm_HandSolder
R57: 4,3k; R_1206_3216Metric_Pad1.30x1.75mm_HandSolder
R58: 2k; R_1206_3216Metric_Pad1.30x1.75mm_HandSolder
R59: 0R; R_1206_3216Metric_Pad1.30x1.75mm_HandSolder
R87: 680R; R_1206_3216Metric_Pad1.30x1.75mm_HandSolder
R88: 1k; R_1206_3216Metric_Pad1.30x1.75mm_HandSolder
U7: LM358; SOIC-8_3.9x4.9mm_P1.27mm

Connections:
+5V: R59.1; also elsewhere on the board
/MController/ZCD: R88.2; also elsewhere on the board
/ZCD/AC: D12.2 (A), D14.1 (K); also elsewhere on the board
/ZCD/~AC: D11.2 (A), D13.1 (K); also elsewhere on the board
GND: C23.2, D13.2 (A), D14.2 (A), D15.1 (K), D24.2 (A), R57.2, R87.2, U7.4 (V-); also elsewhere on the board
unnamed: D11.1 (K), D12.1 (K), R57.1, R58.1
unnamed: D15.2 (A), R55.2, U7.3 (+)
unnamed: D24.1 (K), R56.2, R87.1, R88.1
unnamed: R56.1, U7.1
unnamed: R58.2, U7.2 (-)
unnamed: C23.1, R55.1, R59.2, U7.8 (V+)
